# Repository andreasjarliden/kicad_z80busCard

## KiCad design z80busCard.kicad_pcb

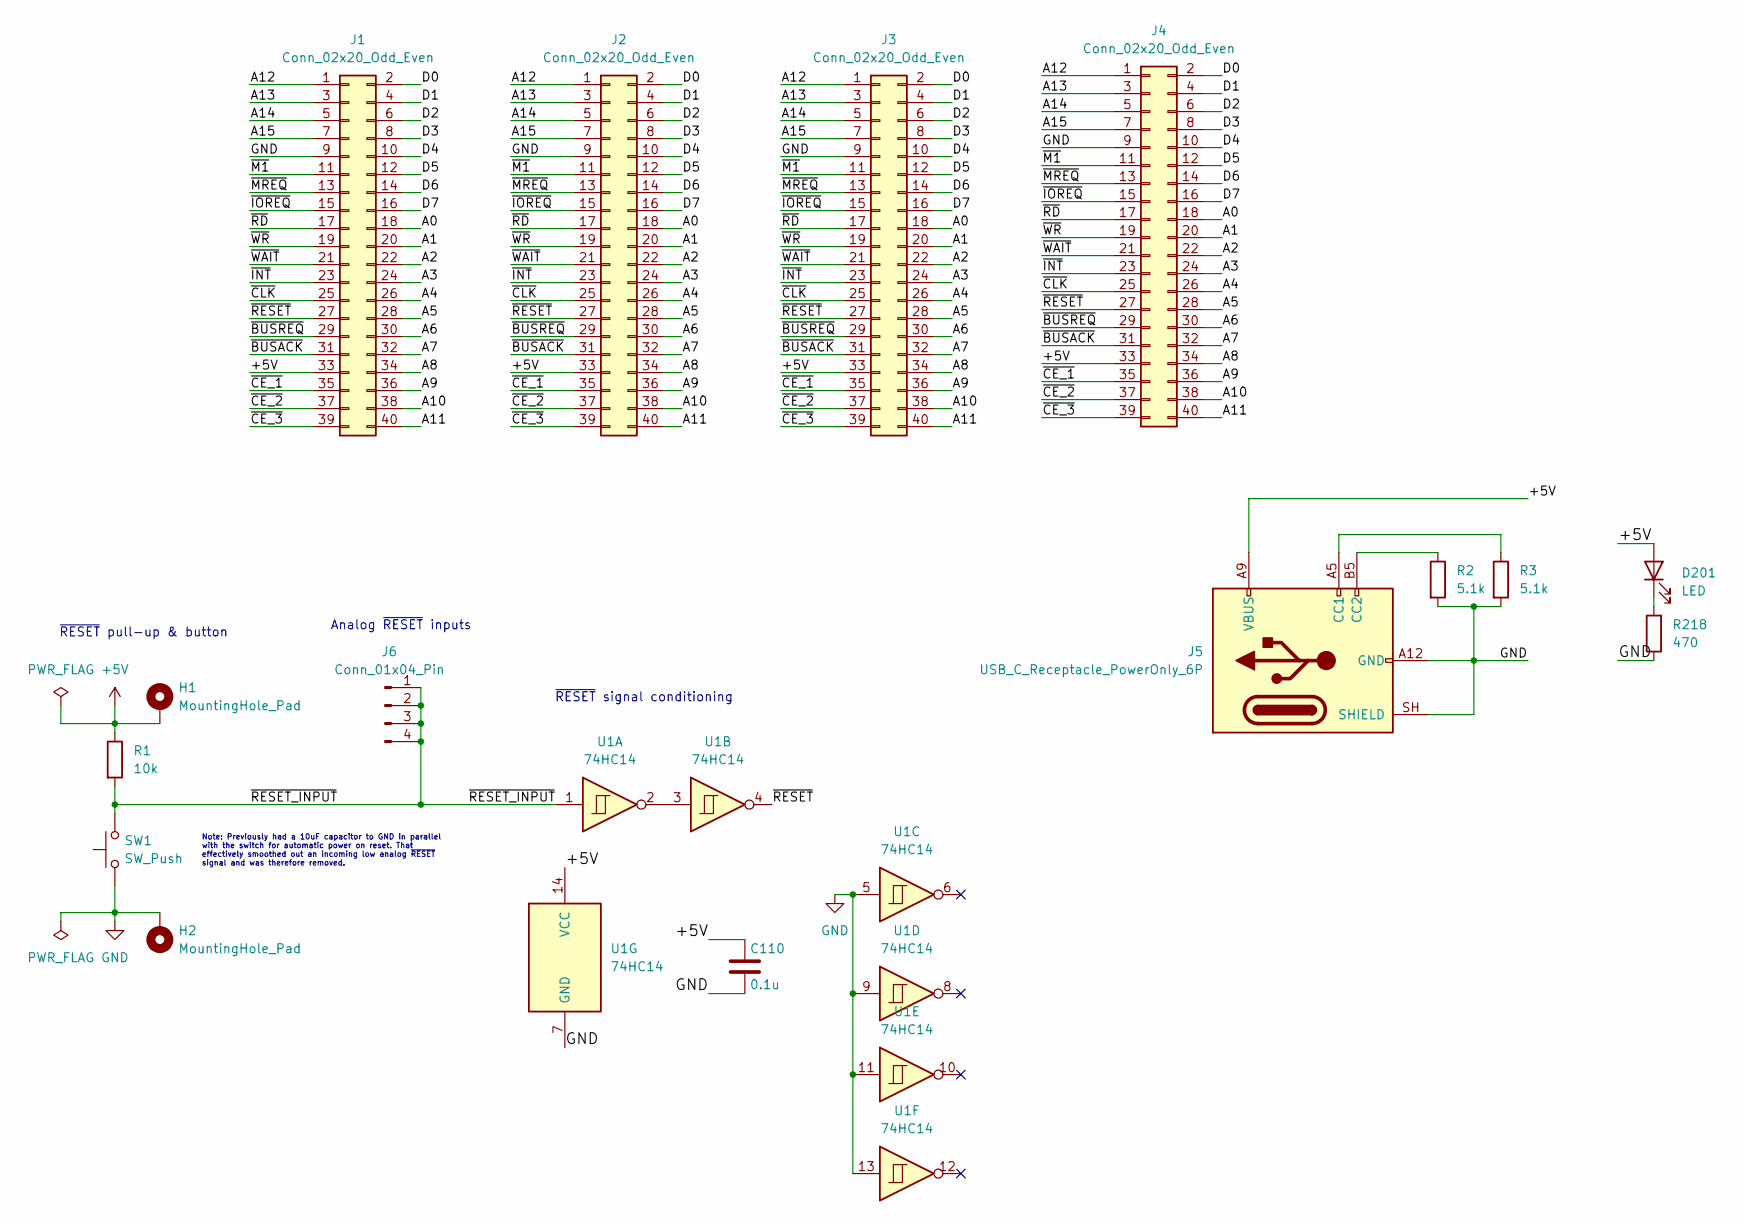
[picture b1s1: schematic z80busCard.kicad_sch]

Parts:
C110: 0.1u; C_0805_2012Metric_Pad1.18x1.45mm_HandSolder
D201: LED; LED_0805_2012Metric_Pad1.15x1.40mm_HandSolder
H1, H2: MountingHole_Pad; MountingHole_4.3mm_M4_ISO14580_Pad_TopBottom
J1, J2, J3: Conn_02x20_Odd_Even; PinSocket_2x20_P2.54mm_Vertical_Mirrored
J4: Conn_02x20_Odd_Even; PinHeader_2x20_P2.54mm_Vertical
J5: USB_C_Receptacle_PowerOnly_6P; USB_C_Receptacle_GCT_USB4125-xx-x_6P_TopMnt_Horizontal
J6: Conn_01x04_Pin; PinHeader_1x04_P2.54mm_Vertical
R1: 10k; R_0805_2012Metric_Pad1.20x1.40mm_HandSolder
R2, R3: 5.1k; R_0805_2012Metric_Pad1.20x1.40mm_HandSolder
R218: 470; R_0805_2012Metric_Pad1.20x1.40mm_HandSolder
SW1: SW_Push; SW_PUSH_6mm_H4.3mm
U1: 74HC14; DIP-14_W7.62mm_Socket

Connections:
+5V: C110.1, D201.2 (A), H1.1 (1_1), J1.33, J2.33, J3.33, J4.33, J5.A9 (VBUS), J5.B9 (VBUS), R1.1, U1.14 (VCC)
/A0: J1.18, J2.18, J3.18, J4.18
/A1: J1.20, J2.20, J3.20, J4.20
/A2: J1.22, J2.22, J3.22, J4.22
/A3: J1.24, J2.24, J3.24, J4.24
/A4: J1.26, J2.26, J3.26, J4.26
/A5: J1.28, J2.28, J3.28, J4.28
/A6: J1.30, J2.30, J3.30, J4.30
/A7: J1.32, J2.32, J3.32, J4.32
/A8: J1.34, J2.34, J3.34, J4.34
/A9: J1.36, J2.36, J3.36, J4.36
/A10: J1.38, J2.38, J3.38, J4.38
/A11: J1.40, J2.40, J3.40, J4.40
/A12: J1.1, J2.1, J3.1, J4.1
/A13: J1.3, J2.3, J3.3, J4.3
/A14: J1.5, J2.5, J3.5, J4.5
/A15: J1.7, J2.7, J3.7, J4.7
/D0: J1.2, J2.2, J3.2, J4.2
/D1: J1.4, J2.4, J3.4, J4.4
/D2: J1.6, J2.6, J3.6, J4.6
/D3: J1.8, J2.8, J3.8, J4.8
/D4: J1.10, J2.10, J3.10, J4.10
/D5: J1.12, J2.12, J3.12, J4.12
/D6: J1.14, J2.14, J3.14, J4.14
/D7: J1.16, J2.16, J3.16, J4.16
/~BUSACK: J1.31, J2.31, J3.31, J4.31
/~BUSREQ: J1.29, J2.29, J3.29, J4.29
/~CE_1: J1.35, J2.35, J3.35, J4.35
/~CE_2: J1.37, J2.37, J3.37, J4.37
/~CE_3: J1.39, J2.39, J3.39, J4.39
/~CLK: J1.25, J2.25, J3.25, J4.25
/~INT: J1.23, J2.23, J3.23, J4.23
/~IOREQ: J1.15, J2.15, J3.15, J4.15
/~M1: J1.11, J2.11, J3.11, J4.11
/~MREQ: J1.13, J2.13, J3.13, J4.13
/~RD: J1.17, J2.17, J3.17, J4.17
/~RESET_INPUT: J6.1, J6.2, J6.3, J6.4, R1.2, SW1.2, U1.1
/~RESET: J1.27, J2.27, J3.27, J4.27, U1.4
/~WAIT: J1.21, J2.21, J3.21, J4.21
/~WR: J1.19, J2.19, J3.19, J4.19
GND: C110.2, H2.1 (1_1), J1.9, J2.9, J3.9, J4.9, J5.A12 (GND), J5.B12 (GND), J5.SH (SHIELD), R2.2, R3.2, R218.1, SW1.1, U1.5, U1.7 (GND), U1.9, U1.11, U1.13
unnamed: D201.1 (K), R218.2
unnamed: J5.A5 (CC1), R3.1
unnamed: J5.B5 (CC2), R2.1
unnamed: U1.2, U1.3

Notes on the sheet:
Note: Previously had a 10uF capacitor to GND in parallel with the switch for automatic power on reset. That effectively smoothed out an incoming low analog ~{RESET} signal and was therefore removed.
~{RESET} pull-up & button
Analog ~{RESET} inputs
~{RESET} signal conditioning

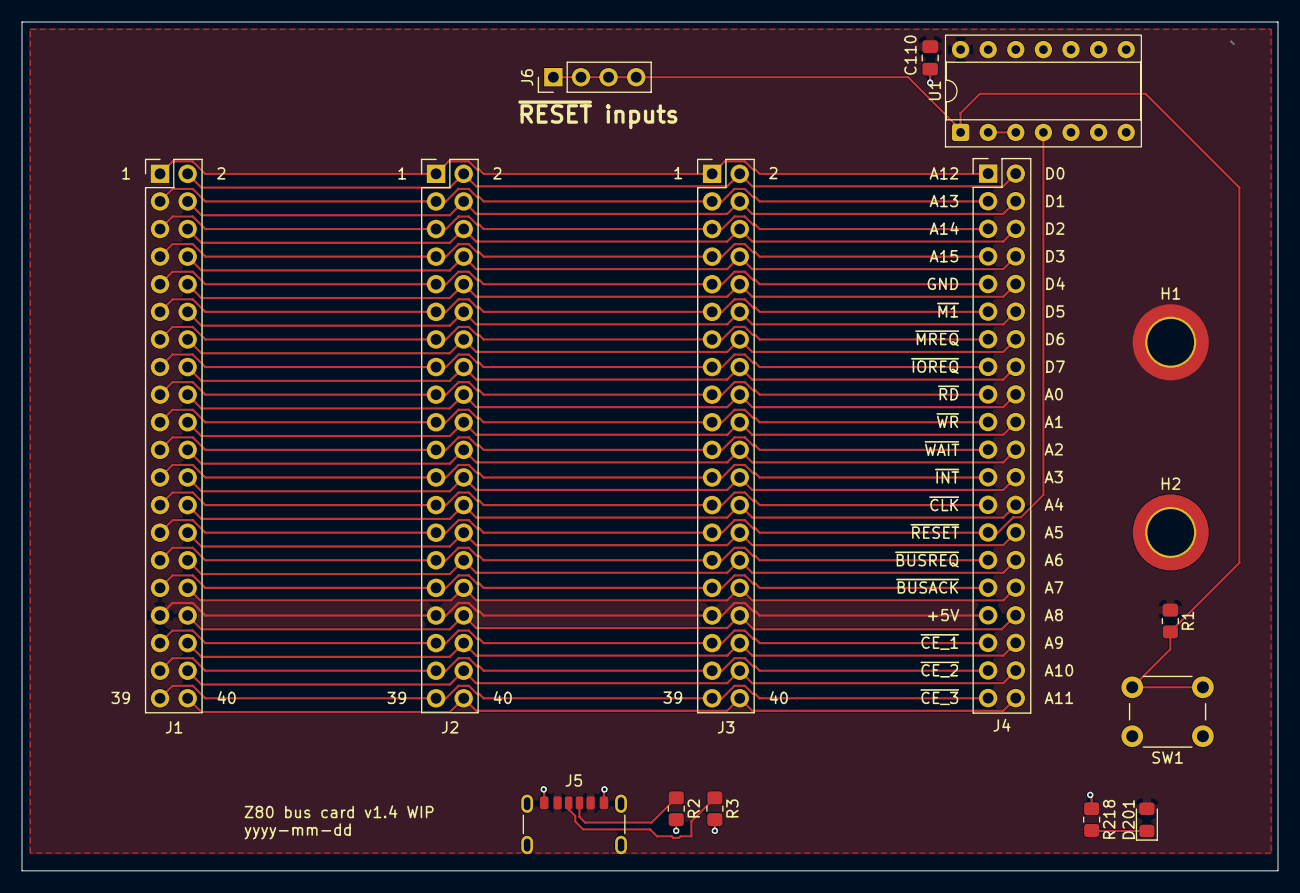
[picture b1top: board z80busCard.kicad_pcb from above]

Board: 2 copper layers, 115.6 x 78.1 mm, 16 parts (0 on the bottom side), 45 nets.

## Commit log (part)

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2025-10-02 Added connectors
2025-10-04 Added reset circuit
2025-10-04 Resistor footprint
2025-10-05 Wired front layer. Added silkscreen labels
2025-10-06 Completed for order
2025-10-19 Fixed USB-C power with pull-downs. Moved connector to the side
2025-12-04 Added power diode
2025-12-04 Added fab folder to .gitignore
2026-05-16 Upgraded to kicad 10, preparing for ground plane
2026-05-17 GND and +5V planes
2026-05-17 Replaced Mounting Hole with Mounting hole pad
2026-05-17 Some cleanup
2026-05-17 Version 1.3 ready for fab
